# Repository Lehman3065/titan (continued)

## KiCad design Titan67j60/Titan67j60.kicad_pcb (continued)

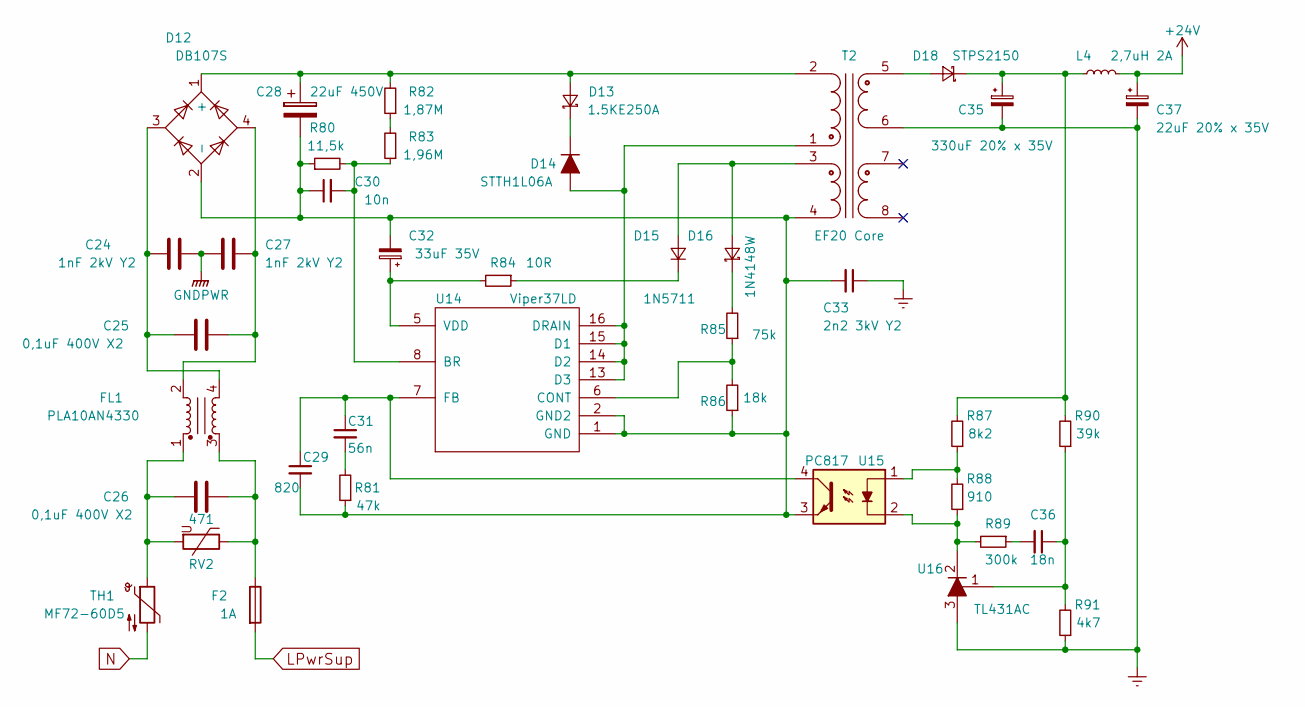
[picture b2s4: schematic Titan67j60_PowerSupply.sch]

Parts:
C24, C27: 1nF 2kV Y2; C_Disc_D10.5mm_W5.0mm_P10.00mm
C25, C26: 0,1uF 400V X2; C_Rect_L16.5mm_W7.0mm_P15.00mm_MKT
C28: 22uF 450V; CP_Radial_D18.0mm_P7.50mm
C29: 820; C_0805
C30: 10n; C_0805
C31: 56n; C_0805
C32: 33uF 35V; CP_Radial_D8.0mm_P2.50mm
C33: 2n2 3kV Y2; C_Disc_D10.5mm_W5.0mm_P10.00mm
C35: 330uF 20% x 35V; CP_Radial_D10.0mm_P5.00mm
C36: 18n; C_0805
C37: 22uF 20% x 35V; CP_Radial_D7.5mm_P2.50mm
D12: DB107S; Diode_Bridge_DFS
D13: 1.5KE250A; D_DO-201_P12.70mm_Horizontal
D14: STTH1L06A; D_SMA
D15: 1N5711; D_SOD-123
D16: 1N4148W; D_SOD-123
D18: STPS2150; D_SMB
F2: 1A; Fuseholder5x20_horiz_open_inline_Type-I
FL1: PLA10AN4330; PLA10AN
L4: 2,7uH 2A; L_Vishay_IHLP-5050
R80: 11,5k; R_0805
R81: 47k; R_0805
R82: 1,87M; R_1206
R83: 1,96M; R_1206
R84: 10R; R_0805
R85: 75k; R_0805
R86: 18k; R_0805
R87: 8k2; R_0805
R88: 910; R_0805
R89: 300k; R_0805
R90: 39k; R_0805
R91: 4k7; R_0805
RV2: 471; RV_Disc_D7_W3.4_P5
T2: EF20 Core; Transformer_Core_EF20
TH1: MF72-60D5; RV_Disc_D7_W3.4_P5
U14: Viper37LD; SOIC-16_3.9x9.9mm_Pitch1.27mm
U15: PC817; DIP-4_W7.62mm
U16: TL431AC; SOT-23

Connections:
+24V: C37.1, L4.2; also elsewhere on the board
Earth: C33.1, C35.2, C37.2, R91.1, T2.6 (SD), U16.3 (A); also elsewhere on the board
FaultOpt1: TH1.2; also elsewhere on the board
GNDPWR: C24.1, C27.2; also elsewhere on the board
LPwrSup: F2.2; also elsewhere on the board
unnamed: C24.2, C25.2, D12.3, FL1.4
unnamed: C25.1, C27.1, D12.4, FL1.2
unnamed: C26.1, F2.1, FL1.3, RV2.1
unnamed: C26.2, FL1.1, RV2.2, TH1.1
unnamed: C28.1, D12.1 (+), D13.2 (A), R82.2, T2.2 (AA)
unnamed: C28.2, C29.2, C30.1, C32.2, C33.2, D12.2 (-), R80.1, R81.1, R86.1, T2.4 (SD), U14.1 (GND), U14.2 (GND2), U15.3
unnamed: C29.1, C31.1, U14.7 (FB), U15.4
unnamed: C30.2, R80.2, R83.1, U14.8 (BR)
unnamed: C31.2, R81.2
unnamed: C32.1, R84.2, U14.5 (VDD)
unnamed: C35.1, D18.1 (K), L4.1, R87.2, R90.2
unnamed: C36.1, R90.1, R91.2, U16.1 (Ref)
unnamed: C36.2, R89.1
unnamed: D13.1 (K), D14.1 (K)
unnamed: D14.2 (A), T2.1 (AB), U14.13 (D3), U14.14 (D2), U14.15 (D1), U14.16 (DRAIN)
unnamed: D15.1 (K), R84.1
unnamed: D15.2 (A), D16.2 (A), T2.3 (SC)
unnamed: D16.1 (K), R85.2
unnamed: D18.2 (A), T2.5 (SC)
unnamed: R82.1, R83.2
unnamed: R85.1, R86.2, U14.6 (CONT)
unnamed: R87.1, R88.2, U15.1
unnamed: R88.1, R89.2, U15.2, U16.2 (K)

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
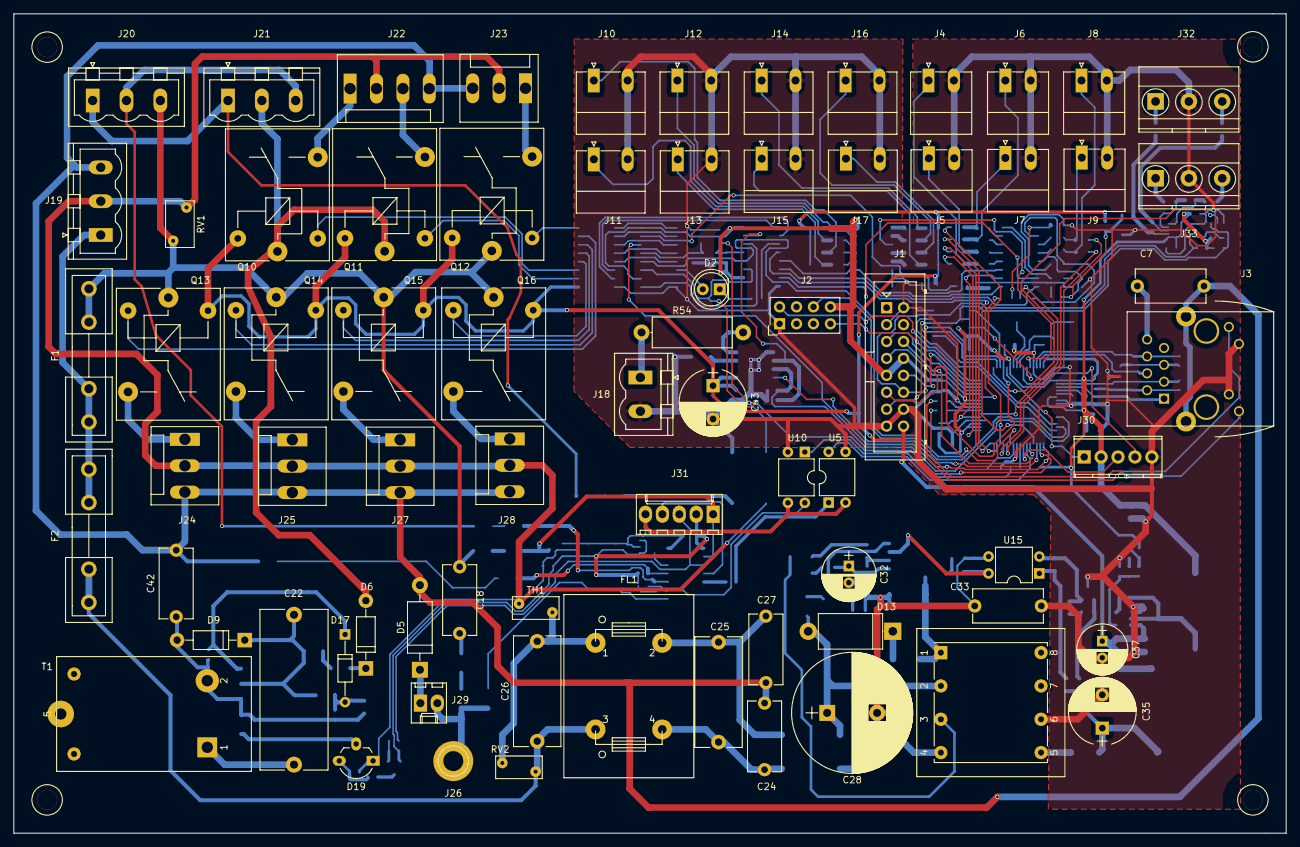
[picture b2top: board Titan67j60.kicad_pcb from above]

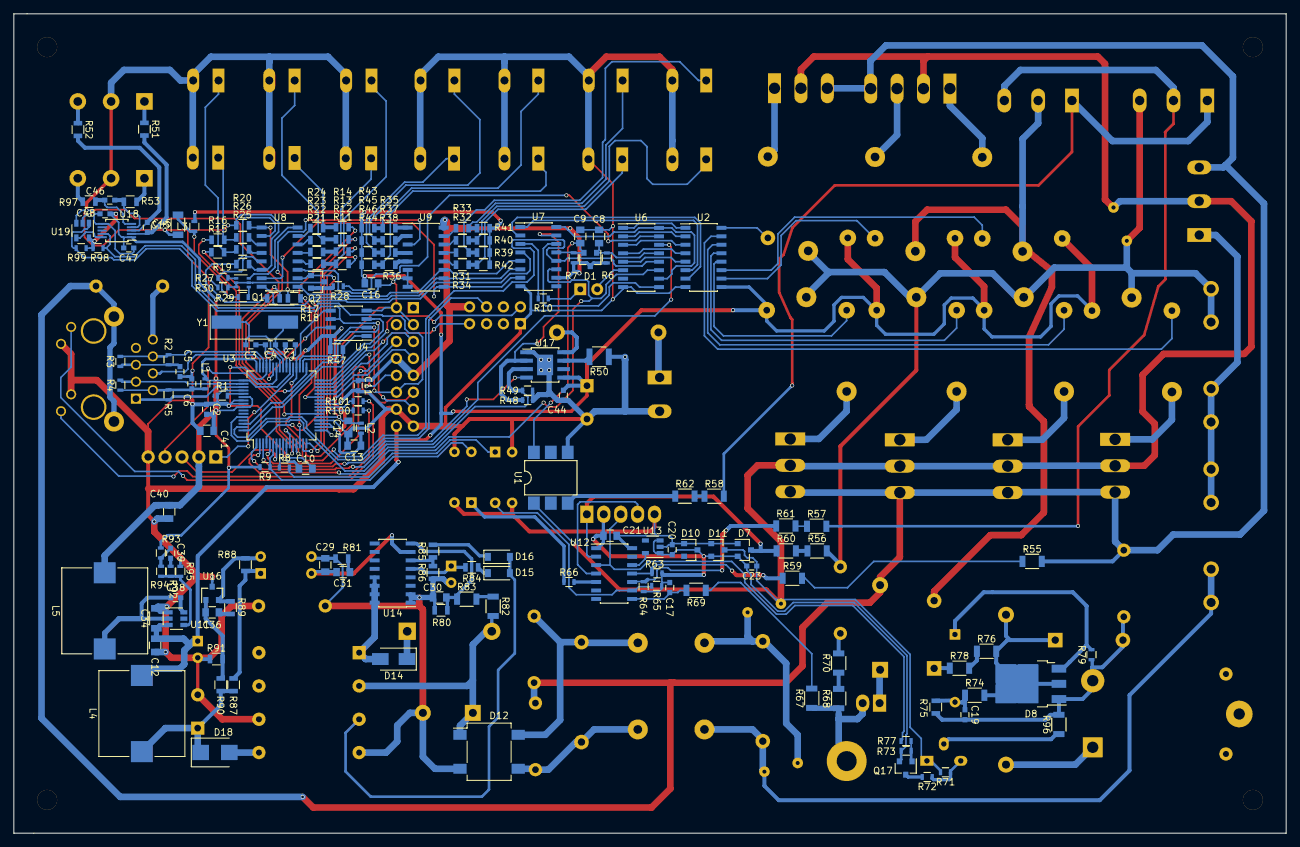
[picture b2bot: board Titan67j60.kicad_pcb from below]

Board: 2 copper layers, 191.0 x 123.0 mm, 242 parts (169 on the bottom side), 202 nets.

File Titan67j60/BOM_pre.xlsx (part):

| U2 | ULN2003D | Housings_SOIC:SOIC-16_3.9x9.9mm_Pitch1.27mm | interface | ULN2003 | / | / | 595D3535
 | C19 | 0,01 | Capacitors_SMD:C_0603 | device | C_Small | /NonSafety/ | /5966F27C/ | 59693D09
 | C23 | 0,047 | Capacitors_SMD:C_0603 | device | C_Small | /NonSafety/ | /5966F27C/ | 59678F65
 | C1 | 0,1 | Capacitors_SMD:C_0603 | device | C_Small | / | / | 595E4B46
 | C11 | 0,1 | Capacitors_SMD:C_0603 | device | C_Small | / | / | 5963EFDC
 | C17 | 0,1 | Capacitors_SMD:C_0603 | device | C_Small | /NonSafety/ | /5966F27C/ | 596753D7
 | C2 | 0,1 | Capacitors_SMD:C_0603 | device | C_Small | / | / | 595E3EE4
 | C20 | 0,1 | Capacitors_SMD:C_0603 | device | C_Small | /NonSafety/ | /5966F27C/ | 59669D1A
 | C38 | 0,1 | Capacitors_SMD:C_0603 | device | C_Small | / | / | 59B05031
 | C44 | 0,1 | Capacitors_SMD:C_0603 | device | C_Small | / | / | 59B44102
 | C47 | 0,1 | Capacitors_SMD:C_0603 | device | C_Small | /AnalogIN/ | /5963ED06/ | 59B8137C
 | C48 | 0,1 | Capacitors_SMD:C_0603 | device | C_Small | /AnalogIN/ | /5963ED06/ | 59B85686
 | C5 | 0,1 | Capacitors_SMD:C_0603 | device | C_Small | / | / | 595E188C
 | C6 | 0,1 | Capacitors_SMD:C_0603 | device | C_Small | / | / | 595E288B
 | C45 | 1500 | Capacitors_SMD:C_0603 | device | C_Small | /AnalogIN/ | /5963ED06/ | 59B7BDDF
 | C46 | 1500 | Capacitors_SMD:C_0603 | device | C_Small | /AnalogIN/ | /5963ED06/ | 59B7D674
 | C3 | 33 | Capacitors_SMD:C_0603 | device | C_Small | / | / | 595E527D
 | C4 | 33 | Capacitors_SMD:C_0603 | device | C_Small | / | / | 595E5312
 | C39 | 75 | Capacitors_SMD:C_0603 | device | C_Small | / | / | 59B0817A
 | C12 | 0,1 | Capacitors_SMD:C_0805 | device | C_Small | / | / | 59660DE1
 | C16 | 0,1uF 50V | Capacitors_SMD:C_0805 | device | C_Small | /AnalogIN/ | /5963ED06/ | 59A632A4
 | C10 | 10,0 | Capacitors_SMD:C_0805 | device | C_Small | / | / | 5963C376
 | C13 | 10,0 | Capacitors_SMD:C_0805 | device | C_Small | / | / | 59660EF2
 | C14 | 10,0 | Capacitors_SMD:C_0805 | device | C_Small | / | / | 59A057FB
 | C21 | 10,0 | Capacitors_SMD:C_0805 | device | C_Small | /NonSafety/ | /5966F27C/ | 596617B2
 | C40 | 10,0 | Capacitors_SMD:C_0805 | device | C_Small | / | / | 59B0C0EB
 | C41 | 10,0 | Capacitors_SMD:C_0805 | device | C_Small | / | / | 59B0C1D6
 | C8 | 10,0 | Capacitors_SMD:C_0805 | device | C_Small | / | / | 595FC963
 | C9 | 10,0 | Capacitors_SMD:C_0805 | device | C_Small | / | / | 595FB228
 | C30 | 10n | Capacitors_SMD:C_0805 | device | C_Small | /PowerSupply/ | /59A41BF3/ | 59A44AED
 | C36 | 18n | Capacitors_SMD:C_0805 | device | C_Small | /PowerSupply/ | /59A41BF3/ | 59A4E157
 | C31 | 56n | Capacitors_SMD:C_0805 | device | C_Small | /PowerSupply/ | /59A41BF3/ | 59A47C73
 | C29 | 820 | Capacitors_SMD:C_0805 | device | C_Small | /PowerSupply/ | /59A41BF3/ | 59A47B9D
 | C34 | 10,0 | Capacitors_SMD:C_1206 | device | C_Small | / | / | 59B0492B
 | C15 | 1uF 50V | Capacitors_SMD:C_1206 | device | C_Small | /AnalogIN/ | /5963ED06/ | 59A623B6
 | C7 | 1nF 2kV | Capacitors_THT:C_Disc_D10.5mm_W5.0mm_P10.00mm | device | C_Small | / | / | 595E0A1B
 | C24 | 1nF 2kV Y2 | Capacitors_THT:C_Disc_D10.5mm_W5.0mm_P10.00mm | device | C | /PowerSupply/ | /59A41BF3/ | 59A5E559
 | C27 | 1nF 2kV Y2 | Capacitors_THT:C_Disc_D10.5mm_W5.0mm_P10.00mm | device | C | /PowerSupply/ | /59A41BF3/ | 59A5EB17
 | C42 | 1nF 2kV Y2 | Capacitors_THT:C_Disc_D10.5mm_W5.0mm_P10.00mm | device | C_Small | /NonSafety/ | /5966F27C/ | 59B3B8B7
 | C18 | 2200x2kV | Capacitors_THT:C_Disc_D10.5mm_W5.0mm_P10.00mm | device | C_Small | /NonSafety/ | /5966F27C/ | 59674C93
 | C33 | 2n2 3kV Y2 | Capacitors_THT:C_Disc_D10.5mm_W5.0mm_P10.00mm | device | C_Small | /PowerSupply/ | /59A41BF3/ | 59A58483
 | C25 | 0,1uF 400V X2 | Capacitors_THT:C_Rect_L16.5mm_W7.0mm_P15.00mm_MKT | device | C | /PowerSupply/ | /59A41BF3/ | 59A44A3B
 | C26 | 0,1uF 400V X2 | Capacitors_THT:C_Rect_L16.5mm_W7.0mm_P15.00mm_MKT | device | C | /PowerSupply/ | /59A41BF3/ | 59A449AE
 | C22 | 1uFx400V | Capacitors_THT:C_Rect_L24.0mm_W10.1mm_P22.50mm_MKT | device | C_Small | /NonSafety/ | /5966F27C/ | 5969502D
 | C35 | 330uF 20% x 35V | Capacitors_THT:CP_Radial_D10.0mm_P5.00mm | device | CP_Small | /PowerSupply/ | /59A41BF3/ | 59A4B5D5
 | C43 | 47uFx50V | Capacitors_THT:CP_Radial_D10.0mm_P5.00mm | device | CP | / | / | 59B42DA4
 | C28 | 22uF 450V | Capacitors_THT:CP_Radial_D18.0mm_P7.50mm | device | CP | /PowerSupply/ | /59A41BF3/ | 59A44B52
 | C37 | 22uF 20% x 35V | Capacitors_THT:CP_Radial_D7.5mm_P2.50mm | device | CP_Small | /PowerSupply/ | /59A41BF3/ | 59A4B727
 | C32 | 33uF 35V | Capacitors_THT:CP_Radial_D8.0mm_P2.50mm | device | CP_Small | /PowerSupply/ | /59A41BF3/ | 59A44BF3
 | J26 | CONN_01X01 | Connectors:1pin | conn | CONN_01X01 | /NonSafety/ | /5966F27C/ | 596757BE
 | J29 | Jamper | Connectors_Molex:Molex_KK-6410-02_02x2.54mm_Straight | conn | CONN_02X01 | /NonSafety/ | /5966F27C/ | 59B36419
 | J31 | CONN_01X05 | Connectors_Molex:Molex_KK-6410-05_05x2.54mm_Straight | conn | CONN_01X05 | /NonSafety/ | /5966F27C/ | 59AAC3A3
 | J1 | CONN_01X16 | Connectors_Multicomp:Multicomp_MC9A12-1634_2x08x2.54mm_Straight | conn | CONN_01X16 | / | / | 595E6982
 | J4 | Termistor 10k | Connectors_Phoenix:PhoenixContact_MC-G_02x3.81mm_Angled | conn | CONN_01X02 | /AnalogIN/ | /5963ED06/ | 59643E7A
 | J5 | Termistor 10k | Connectors_Phoenix:PhoenixContact_MC-G_02x3.81mm_Angled | conn | CONN_01X02 | /AnalogIN/ | /5963ED06/ | 596440DF
 | J6 | Termistor 10k | Connectors_Phoenix:PhoenixContact_MC-G_02x3.81mm_Angled | conn | CONN_01X02 | /AnalogIN/ | /5963ED06/ | 59644126
 | J7 | Termistor 10k | Connectors_Phoenix:PhoenixContact_MC-G_02x3.81mm_Angled | conn | CONN_01X02 | /AnalogIN/ | /5963ED06/ | 5964416C
 | J8 | Termistor 10k | Connectors_Phoenix:PhoenixContact_MC-G_02x3.81mm_Angled | conn | CONN_01X02 | /AnalogIN/ | /5963ED06/ | 596441B9
 | J9 | Termistor 10k | Connectors_Phoenix:PhoenixContact_MC-G_02x3.81mm_Angled | conn | CONN_01X02 | /AnalogIN/ | /5963ED06/ | 59644205
 | J10 | Termistor 10k | Connectors_Phoenix:PhoenixContact_MC-G_02x5.08mm_Angled | conn | CONN_01X02 | /AnalogIN/ | /5963ED06/ | 59657630
 | J11 | Termistor 10k | Connectors_Phoenix:PhoenixContact_MC-G_02x5.08mm_Angled | conn | CONN_01X02 | /AnalogIN/ | /5963ED06/ | 59657637
 | J12 | Termistor 10k | Connectors_Phoenix:PhoenixContact_MC-G_02x5.08mm_Angled | conn | CONN_01X02 | /AnalogIN/ | /5963ED06/ | 5965763E
 | J13 | Termistor 10k | Connectors_Phoenix:PhoenixContact_MC-G_02x5.08mm_Angled | conn | CONN_01X02 | /AnalogIN/ | /5963ED06/ | 59657645
 | J14 | Termistor 10k | Connectors_Phoenix:PhoenixContact_MC-G_02x5.08mm_Angled | conn | CONN_01X02 | /AnalogIN/ | /5963ED06/ | 5965764C
 | J15 | Termistor 10k | Connectors_Phoenix:PhoenixContact_MC-G_02x5.08mm_Angled | conn | CONN_01X02 | /AnalogIN/ | /5963ED06/ | 59657653
 | J16 | Termistor 10k | Connectors_Phoenix:PhoenixContact_MC-G_02x5.08mm_Angled | conn | CONN_01X02 | /AnalogIN/ | /5963ED06/ | 59657A73
 | J17 | Termistor 10k | Connectors_Phoenix:PhoenixContact_MC-G_02x5.08mm_Angled | conn | CONN_01X02 | /AnalogIN/ | /5963ED06/ | 59657AFF
 | J18 | CONN_01X02 | Connectors_Phoenix:PhoenixContact_MSTBVA-G_02x5.08mm_Vertical | conn | CONN_01X02 | / | / | 599E5398
 | J19 | CONN_01X03 | Connectors_Phoenix:PhoenixContact_MSTBVA-G_03x5.08mm_Vertical | conn | CONN_01X03 | /NonSafety/ | /5966F27C/ | 59660F69
 | J20 | CONN_01X03 | Connectors_Phoenix:PhoenixContact_MSTBVA-G_03x5.08mm_Vertical | conn | CONN_01X03 | /NonSafety/ | /5966F27C/ | 5966FBBF
 | J21 | CONN_01X03 | Connectors_Phoenix:PhoenixContact_MSTBVA-G_03x5.08mm_Vertical | conn | CONN_01X03 | /NonSafety/ | /5966F27C/ | 596644C6
 | J2 | WiFi/GSM | Connectors_Samtec:SDL-108-X-XX_2x04 | conn | CONN_02X04 | / | / | 595E6ACC
 | J32 | CONN_01X03 | Connectors_Terminal_Blocks:TerminalBlock_Pheonix_MKDS1.5-3pol | conn | CONN_01X03 | /AnalogIN/ | /5963ED06/ | 59B7E2F3
 | J33 | CONN_01X03 | Connectors_Terminal_Blocks:TerminalBlock_Pheonix_MKDS1.5-3pol | conn | CONN_01X03 | /AnalogIN/ | /5963ED06/ | 59B7E47E
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
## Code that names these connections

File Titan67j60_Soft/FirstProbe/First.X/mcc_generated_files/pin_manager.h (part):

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// get/set LedA aliases
#define LedA_TRIS               TRISAbits.TRISA0
#define LedA_LAT                LATAbits.LATA0
#define LedA_PORT               PORTAbits.RA0
#define LedA_ANS                anselRA0bits.anselRA0
#define LedA_SetHigh()            do { LATAbits.LATA0 = 1; } while(0)
#define LedA_SetLow()             do { LATAbits.LATA0 = 0; } while(0)
#define LedA_Toggle()             do { LATAbits.LATA0 = ~LATAbits.LATA0; } while(0)
#define LedA_GetValue()           PORTAbits.RA0
#define LedA_SetDigitalInput()    do { TRISAbits.TRISA0 = 1; } while(0)
#define LedA_SetDigitalOutput()   do { TRISAbits.TRISA0 = 0; } while(0)
#define LedA_SetAnalogMode()  do { anselRA0bits.anselRA0 = 1; } while(0)
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// get/set LedB aliases
#define LedB_TRIS               TRISAbits.TRISA1
#define LedB_LAT                LATAbits.LATA1
#define LedB_PORT               PORTAbits.RA1
#define LedB_ANS                anselRA1bits.anselRA1
#define LedB_SetHigh()            do { LATAbits.LATA1 = 1; } while(0)
#define LedB_SetLow()             do { LATAbits.LATA1 = 0; } while(0)
#define LedB_Toggle()             do { LATAbits.LATA1 = ~LATAbits.LATA1; } while(0)
#define LedB_GetValue()           PORTAbits.RA1
#define LedB_SetDigitalInput()    do { TRISAbits.TRISA1 = 1; } while(0)
#define LedB_SetDigitalOutput()   do { TRISAbits.TRISA1 = 0; } while(0)
#define LedB_SetAnalogMode()  do { anselRA1bits.anselRA1 = 1; } while(0)
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// get/set channel_Ref5k1 aliases
#define channel_Ref5k1_TRIS               TRISAbits.TRISA2
#define channel_Ref5k1_LAT                LATAbits.LATA2
#define channel_Ref5k1_PORT               PORTAbits.RA2
#define channel_Ref5k1_ANS                anselRA2bits.anselRA2
#define channel_Ref5k1_SetHigh()            do { LATAbits.LATA2 = 1; } while(0)
#define channel_Ref5k1_SetLow()             do { LATAbits.LATA2 = 0; } while(0)
#define channel_Ref5k1_Toggle()             do { LATAbits.LATA2 = ~LATAbits.LATA2; } while(0)
#define channel_Ref5k1_GetValue()           PORTAbits.RA2
#define channel_Ref5k1_SetDigitalInput()    do { TRISAbits.TRISA2 = 1; } while(0)
#define channel_Ref5k1_SetDigitalOutput()   do { TRISAbits.TRISA2 = 0; } while(0)
#define channel_Ref5k1_SetAnalogMode()  do { anselRA2bits.anselRA2 = 1; } while(0)
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#define RA3_SetHigh()    do { LATAbits.LATA3 = 1; } while(0)
#define RA3_SetLow()   do { LATAbits.LATA3 = 0; } while(0)
#define RA3_Toggle()   do { LATAbits.LATA3 = ~LATAbits.LATA3; } while(0)
#define RA3_GetValue()         PORTAbits.RA3
#define RA3_SetDigitalInput()   do { TRISAbits.TRISA3 = 1; } while(0)
#define RA3_SetDigitalOutput()  do { TRISAbits.TRISA3 = 0; } while(0)
#define RA3_SetAnalogMode() do { anselRA3bits.anselRA3 = 1; } while(0)
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// get/set DispSerMode aliases
#define DispSerMode_TRIS               TRISAbits.TRISA4
#define DispSerMode_LAT                LATAbits.LATA4
#define DispSerMode_PORT               PORTAbits.RA4
#define DispSerMode_SetHigh()            do { LATAbits.LATA4 = 1; } while(0)
#define DispSerMode_SetLow()             do { LATAbits.LATA4 = 0; } while(0)
#define DispSerMode_Toggle()             do { LATAbits.LATA4 = ~LATAbits.LATA4; } while(0)
#define DispSerMode_GetValue()           PORTAbits.RA4
#define DispSerMode_SetDigitalInput()    do { TRISAbits.TRISA4 = 1; } while(0)
#define DispSerMode_SetDigitalOutput()   do { TRISAbits.TRISA4 = 0; } while(0)

// get/set channel_Ref33k aliases
#define channel_Ref33k_TRIS               TRISAbits.TRISA5
#define channel_Ref33k_LAT                LATAbits.LATA5
#define channel_Ref33k_PORT               PORTAbits.RA5
#define channel_Ref33k_ANS                anselRA5bits.anselRA5
#define channel_Ref33k_SetHigh()            do { LATAbits.LATA5 = 1; } while(0)
#define channel_Ref33k_SetLow()             do { LATAbits.LATA5 = 0; } while(0)
#define channel_Ref33k_Toggle()             do { LATAbits.LATA5 = ~LATAbits.LATA5; } while(0)
#define channel_Ref33k_GetValue()           PORTAbits.RA5
#define channel_Ref33k_SetDigitalInput()    do { TRISAbits.TRISA5 = 1; } while(0)
#define channel_Ref33k_SetDigitalOutput()   do { TRISAbits.TRISA5 = 0; } while(0)
#define channel_Ref33k_SetAnalogMode()  do { anselRA5bits.anselRA5 = 1; } while(0)
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// get/set NoPWMFault aliases
#define NoPWMFault_TRIS               TRISBbits.TRISB0
#define NoPWMFault_LAT                LATBbits.LATB0
#define NoPWMFault_PORT               PORTBbits.RB0
#define NoPWMFault_SetHigh()            do { LATBbits.LATB0 = 1; } while(0)
#define NoPWMFault_SetLow()             do { LATBbits.LATB0 = 0; } while(0)
#define NoPWMFault_Toggle()             do { LATBbits.LATB0 = ~LATBbits.LATB0; } while(0)
#define NoPWMFault_GetValue()           PORTBbits.RB0
#define NoPWMFault_SetDigitalInput()    do { TRISBbits.TRISB0 = 1; } while(0)
#define NoPWMFault_SetDigitalOutput()   do { TRISBbits.TRISB0 = 0; } while(0)

// get/set NoHiVFault aliases
#define NoHiVFault_TRIS               TRISBbits.TRISB1
#define NoHiVFault_LAT                LATBbits.LATB1
#define NoHiVFault_PORT               PORTBbits.RB1
#define NoHiVFault_SetHigh()            do { LATBbits.LATB1 = 1; } while(0)
#define NoHiVFault_SetLow()             do { LATBbits.LATB1 = 0; } while(0)
#define NoHiVFault_Toggle()             do { LATBbits.LATB1 = ~LATBbits.LATB1; } while(0)
#define NoHiVFault_GetValue()           PORTBbits.RB1
#define NoHiVFault_SetDigitalInput()    do { TRISBbits.TRISB1 = 1; } while(0)
#define NoHiVFault_SetDigitalOutput()   do { TRISBbits.TRISB1 = 0; } while(0)

// get/set DispInt aliases
#define DispInt_TRIS               TRISBbits.TRISB2
#define DispInt_LAT                LATBbits.LATB2
#define DispInt_PORT               PORTBbits.RB2
#define DispInt_SetHigh()            do { LATBbits.LATB2 = 1; } while(0)
#define DispInt_SetLow()             do { LATBbits.LATB2 = 0; } while(0)
#define DispInt_Toggle()             do { LATBbits.LATB2 = ~LATBbits.LATB2; } while(0)
#define DispInt_GetValue()           PORTBbits.RB2
#define DispInt_SetDigitalInput()    do { TRISBbits.TRISB2 = 1; } while(0)
#define DispInt_SetDigitalOutput()   do { TRISBbits.TRISB2 = 0; } while(0)

// get/set SerialLinkIn aliases
#define SerialLinkIn_TRIS               TRISBbits.TRISB3
#define SerialLinkIn_LAT                LATBbits.LATB3
#define SerialLinkIn_PORT               PORTBbits.RB3
#define SerialLinkIn_SetHigh()            do { LATBbits.LATB3 = 1; } while(0)
#define SerialLinkIn_SetLow()             do { LATBbits.LATB3 = 0; } while(0)
#define SerialLinkIn_Toggle()             do { LATBbits.LATB3 = ~LATBbits.LATB3; } while(0)
#define SerialLinkIn_GetValue()           PORTBbits.RB3
#define SerialLinkIn_SetDigitalInput()    do { TRISBbits.TRISB3 = 1; } while(0)
#define SerialLinkIn_SetDigitalOutput()   do { TRISBbits.TRISB3 = 0; } while(0)

// get/set DigIn aliases
#define DigIn_TRIS               TRISBbits.TRISB4
#define DigIn_LAT                LATBbits.LATB4
#define DigIn_PORT               PORTBbits.RB4
#define DigIn_SetHigh()            do { LATBbits.LATB4 = 1; } while(0)
#define DigIn_SetLow()             do { LATBbits.LATB4 = 0; } while(0)
#define DigIn_Toggle()             do { LATBbits.LATB4 = ~LATBbits.LATB4; } while(0)
#define DigIn_GetValue()           PORTBbits.RB4
#define DigIn_SetDigitalInput()    do { TRISBbits.TRISB4 = 1; } while(0)
#define DigIn_SetDigitalOutput()   do { TRISBbits.TRISB4 = 0; } while(0)

// get/set NoFlashHold aliases
#define NoFlashHold_TRIS               TRISBbits.TRISB5
#define NoFlashHold_LAT                LATBbits.LATB5
#define NoFlashHold_PORT               PORTBbits.RB5
#define NoFlashHold_SetHigh()            do { LATBbits.LATB5 = 1; } while(0)
#define NoFlashHold_SetLow()             do { LATBbits.LATB5 = 0; } while(0)
#define NoFlashHold_Toggle()             do { LATBbits.LATB5 = ~LATBbits.LATB5; } while(0)
#define NoFlashHold_GetValue()           PORTBbits.RB5
#define NoFlashHold_SetDigitalInput()    do { TRISBbits.TRISB5 = 1; } while(0)
#define NoFlashHold_SetDigitalOutput()   do { TRISBbits.TRISB5 = 0; } while(0)

// get/set PGC aliases
#define PGC_TRIS               TRISBbits.TRISB6
#define PGC_LAT                LATBbits.LATB6
#define PGC_PORT               PORTBbits.RB6
#define PGC_SetHigh()            do { LATBbits.LATB6 = 1; } while(0)
#define PGC_SetLow()             do { LATBbits.LATB6 = 0; } while(0)
#define PGC_Toggle()             do { LATBbits.LATB6 = ~LATBbits.LATB6; } while(0)
#define PGC_GetValue()           PORTBbits.RB6
#define PGC_SetDigitalInput()    do { TRISBbits.TRISB6 = 1; } while(0)
#define PGC_SetDigitalOutput()   do { TRISBbits.TRISB6 = 0; } while(0)

// get/set PGD aliases
#define PGD_TRIS               TRISBbits.TRISB7
#define PGD_LAT                LATBbits.LATB7
#define PGD_PORT               PORTBbits.RB7
#define PGD_SetHigh()            do { LATBbits.LATB7 = 1; } while(0)
#define PGD_SetLow()             do { LATBbits.LATB7 = 0; } while(0)
#define PGD_Toggle()             do { LATBbits.LATB7 = ~LATBbits.LATB7; } while(0)
#define PGD_GetValue()           PORTBbits.RB7
#define PGD_SetDigitalInput()    do { TRISBbits.TRISB7 = 1; } while(0)
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
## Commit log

2017-10-25 Начальное сотояние проекта
2017-11-09 добавил в Readme githab и сгенерил МСС для TCP/IP: UDP + DHCP
2017-12-01 Microchip стек мигает светодиодом и получает IP адрес
2018-04-18 FirstProbe - мигает в локалке (XC8), SecondProbe - собирает TCP стек с HTTP2 (C18), FhirdProbe - пробуем с нуля писать без TCP стека (C18) TitanNonSafety - для ATtiny20 на высоковольтной стороне
2018-06-25 Работает минимальный набор до прикручивания TCP IP
